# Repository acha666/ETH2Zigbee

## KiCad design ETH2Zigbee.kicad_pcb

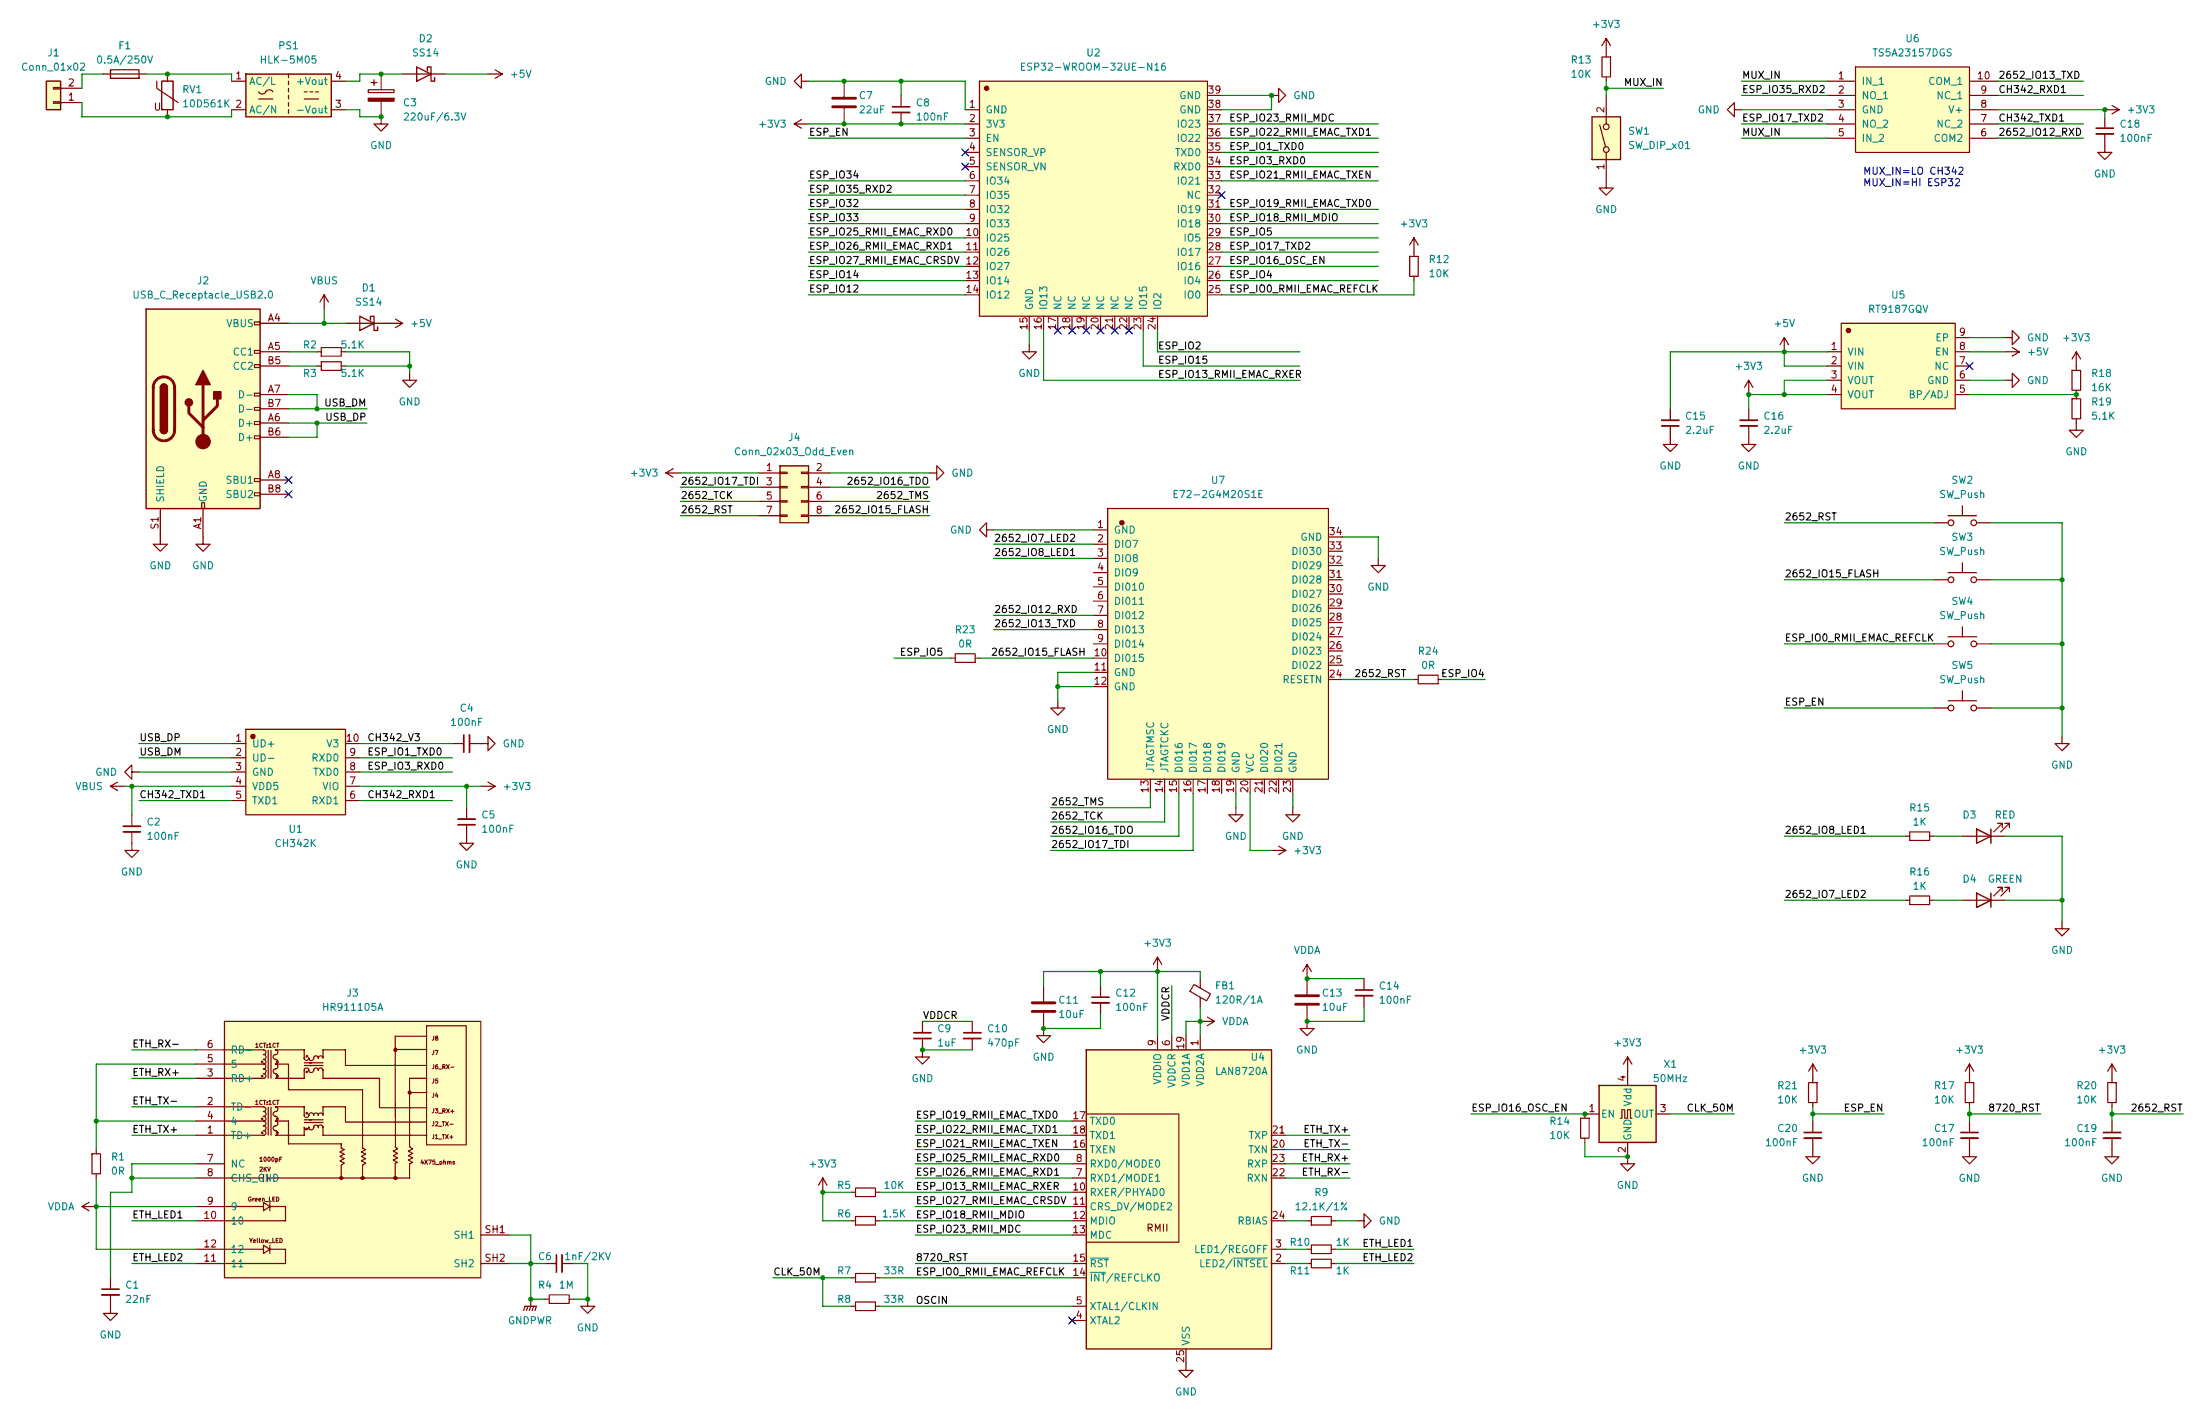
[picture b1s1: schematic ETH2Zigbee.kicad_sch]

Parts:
C1: 22nF; C_0402_1005Metric
C2, C4, C5, C8, C12, C14, C17, C18, C19, C20: 100nF; C_0402_1005Metric
C3: 220uF/6.3V; CP_Elec_6.3x5.4
C6: 1nF/2KV; C_1206_3216Metric
C7: 22uF; C_0603_1608Metric
C9: 1uF; C_0402_1005Metric
C10: 470pF; C_0402_1005Metric
C11, C13: 10uF; C_0603_1608Metric
C15, C16: 2.2uF; C_0402_1005Metric
D1, D2: SS14; D_SMA
D3: RED; LED_0402_1005Metric
D4: GREEN; LED_0402_1005Metric
F1: 0.5A/250V; Fuseholder_Littelfuse_Nano2_154x
FB1: 120R/1A; L_0402_1005Metric
J1: Conn_01x02; CONN-TH_2P-P5.00_WJ500V-5.08-2P
J2: USB_C_Receptacle_USB2.0; USB_C_Receptacle_XKB_U262-16XN-4BVC11
J3: HR911105A; RJ45-TH_HR911105A
J4: Conn_02x03_Odd_Even; PinHeader_2x04_P2.54mm_Vertical
PS1: HLK-5M05; PWRM-TH_HLK-5M05
R1, R23, R24: 0R; R_0402_1005Metric
R2, R3, R19: 5.1K; R_0402_1005Metric
R4: 1M; R_1206_3216Metric
R5, R12, R13, R14, R17, R20, R21: 10K; R_0402_1005Metric
R6: 1.5K; R_0402_1005Metric
R7, R8: 33R; R_0402_1005Metric
R9: 12.1K/1%; R_0402_1005Metric
R10, R11, R15, R16: 1K; R_0402_1005Metric
R18: 16K; R_0402_1005Metric
RV1: 10D561K; RV_Disc_D12mm_W7.1mm_P7.5mm
SW1: SW_DIP_x01; SW_DIP_SPSTx01_Slide_Copal_CHS-01A_W5.08mm_P1.27mm_JPin
SW2, SW3, SW4, SW5: SW_Push; SW_Push_SPST_NO_Alps_SKRK
U1: CH342K; SSOP-10_3.9x4.9mm_P1.00mm
U2: ESP32-WROOM-32UE-N16; WIFI-SMD_ESP32-WROOM-32E
U4: LAN8720A; VQFN-24-1EP_4x4mm_P0.5mm_EP2.5x2.5mm_ThermalVias
U5: RT9187GQV; DFN-8-1EP_3x3mm_P0.65mm_EP1.55x2.4mm
U6: TS5A23157DGS; MSOP-10_3x3mm_P0.5mm
U7: E72-2G4M20S1E; WIRELM-SMD_E72-2G4M20S1E
X1: 50MHz; Oscillator_SMD_Abracon_ASE-4Pin_3.2x2.5mm

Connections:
+3V3: C5.2, C7.2, C8.2, C11.1, C12.1, C16.2, C18.1, FB1.1, J4.1, R5.1, R6.1, R12.1, R13.1, R17.1, R18.1, R20.1, R21.1, U1.7 (VIO), U2.2 (3V3), U4.9 (VDDIO), U5.3 (VOUT), U5.4 (VOUT), U6.8 (V+), U7.20 (VCC), X1.4 (Vdd)
+5V: C15.2, D1.1 (K), D2.1 (K), U5.1 (VIN), U5.2 (VIN), U5.8 (EN)
/2652_IO7_LED2: R16.1, U7.2 (DIO7)
/2652_IO8_LED1: R15.1, U7.3 (DIO8)
/2652_IO12_RXD: U6.6 (COM2), U7.7 (DI012)
/2652_IO13_TXD: U6.10 (COM_1), U7.8 (DI013)
/2652_IO15_FLASH: J4.8, R23.1, SW3.1, U7.10 (DI015)
/2652_IO16_TDO: J4.4, U7.15 (DI016)
/2652_IO17_TDI: J4.3, U7.16 (DI017)
/2652_RST: C19.1, J4.7, R20.2, R24.2, SW2.1, U7.24 (RESETN)
/2652_TCK: J4.5, U7.14 (JTAGTCKC)
/2652_TMS: J4.6, U7.13 (JTAGTMSC)
/8720_RST: C17.1, R17.2, U4.15 (~RST)
/CH342_RXD1: U1.6 (RXD1), U6.9 (NC_1)
/CH342_TXD1: U1.5 (TXD1), U6.7 (NC_2)
/CH342_V3: C4.1, U1.10 (V3)
/CLK_50M: R7.1, R8.1, X1.3 (OUT)
/ESP_EN: C20.1, R21.2, SW5.1, U2.3 (EN)
/ESP_IO0_RMII_EMAC_REFCLK: R7.2, R12.2, SW4.1, U2.25 (IO0), U4.14 (~INT/REFCLKO)
/ESP_IO1_TXD0: U1.9 (RXD0), U2.35 (TXD0)
/ESP_IO2: U2.24 (IO2)
/ESP_IO3_RXD0: U1.8 (TXD0), U2.34 (RXD0)
/ESP_IO4: R24.1, U2.26 (IO4)
/ESP_IO5: R23.2, U2.29 (IO5)
/ESP_IO12: U2.14 (IO12)
/ESP_IO13_RMII_EMAC_RXER: R5.2, U2.16 (IO13), U4.10 (RXER/PHYAD0)
/ESP_IO14: U2.13 (IO14)
/ESP_IO15: U2.23 (IO15)
/ESP_IO16_OSC_EN: R14.1, U2.27 (IO16), X1.1 (EN)
/ESP_IO17_TXD2: U2.28 (IO17), U6.4 (NO_2)
/ESP_IO18_RMII_MDIO: R6.2, U2.30 (IO18), U4.12 (MDIO)
/ESP_IO19_RMII_EMAC_TXD0: U2.31 (IO19), U4.17 (TXD0)
/ESP_IO21_RMII_EMAC_TXEN: U2.33 (IO21), U4.16 (TXEN)
/ESP_IO22_RMII_EMAC_TXD1: U2.36 (IO22), U4.18 (TXD1)
/ESP_IO23_RMII_MDC: U2.37 (IO23), U4.13 (MDC)
/ESP_IO25_RMII_EMAC_RXD0: U2.10 (IO25), U4.8 (RXD0/MODE0)
/ESP_IO26_RMII_EMAC_RXD1: U2.11 (IO26), U4.7 (RXD1/MODE1)
/ESP_IO27_RMII_EMAC_CRSDV: U2.12 (IO27), U4.11 (CRS_DV/MODE2)
/ESP_IO32: U2.8 (IO32)
/ESP_IO33: U2.9 (IO33)
/ESP_IO34: U2.6 (IO34)
/ESP_IO35_RXD2: U2.7 (IO35), U6.2 (NO_1)
/ETH_LED1: J3.10, R10.2
/ETH_LED2: J3.11, R11.2
/ETH_RX+: J3.3 (RD+), U4.23 (RXP)
/ETH_RX-: J3.6 (RD-), U4.22 (RXN)
/ETH_TX+: J3.1 (TD+), U4.21 (TXP)
/ETH_TX-: J3.2 (TD-), U4.20 (TXN)
/MUX_IN: R13.2, SW1.2, U6.1 (IN_1), U6.5 (IN_2)
/OSCIN: R8.2, U4.5 (XTAL1/CLKIN)
/USB_DM: J2.A7 (D-), J2.B7 (D-), U1.2 (UD-)
/USB_DP: J2.A6 (D+), J2.B6 (D+), U1.1 (UD+)
/VDDCR: C9.1, C10.1, U4.6 (VDDCR)
GND: C1.2, C2.1, C3.2, C4.2, C5.1, C6.2, C7.1, C8.1, C9.2, C10.2, C11.2, C12.2, C13.2, C14.2, C15.1, C16.1, C17.2, C18.2, C19.2, C20.2, D3.1 (K), D4.1 (K), J2.A1 (GND), J2.A12 (GND), J2.B1 (GND), J2.B12 (GND), J2.S1 (SHIELD), J4.2, PS1.3 (-Vout), R2.2, R3.2, R4.2, R9.2, R14.2, R19.2, SW1.1, SW2.2, SW3.2, SW4.2, SW5.2, U1.3 (GND), U2.1 (GND), U2.15 (GND), U2.38 (GND), U2.39 (GND), U4.25 (VSS), U5.6 (GND), U5.9 (EP), U6.3 (GND), U7.1 (GND), U7.11 (GND), U7.12 (GND), U7.19 (GND), U7.23 (GND), U7.34 (GND), X1.2 (GND)
GNDPWR: C6.1, J3.SH1, J3.SH2, R4.1
unnamed: C3.1, D2.2 (A), PS1.4 (+Vout)
unnamed: D3.2 (A), R15.2
unnamed: D4.2 (A), R16.2
unnamed: J1.1, PS1.2 (AC/N), RV1.2
unnamed: F1.1, J1.2
unnamed: J2.A5 (CC1), R2.1
unnamed: J2.B5 (CC2), R3.1
unnamed: C1.1, J3.7 (NC), J3.8 (CHS_GND)
unnamed: J3.4, J3.5, R1.1
unnamed: F1.2, PS1.1 (AC/L), RV1.1
unnamed: R10.1, U4.3 (LED1/REGOFF)
unnamed: R11.1, U4.2 (LED2/~INTSEL)
unnamed: R9.1, U4.24 (RBIAS)
unnamed: R18.2, R19.1, U5.5 (BP/ADJ)
VBUS: C2.2, D1.2 (A), J2.A4 (VBUS), J2.A9 (VBUS), J2.B4 (VBUS), J2.B9 (VBUS), U1.4 (VDD5)
VDDA: C13.1, C14.1, FB1.2, J3.9, J3.12, R1.2, U4.1 (VDD2A), U4.19 (VDD1A)

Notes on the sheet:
MUX_IN=LO CH342 MUX_IN=HI ESP32

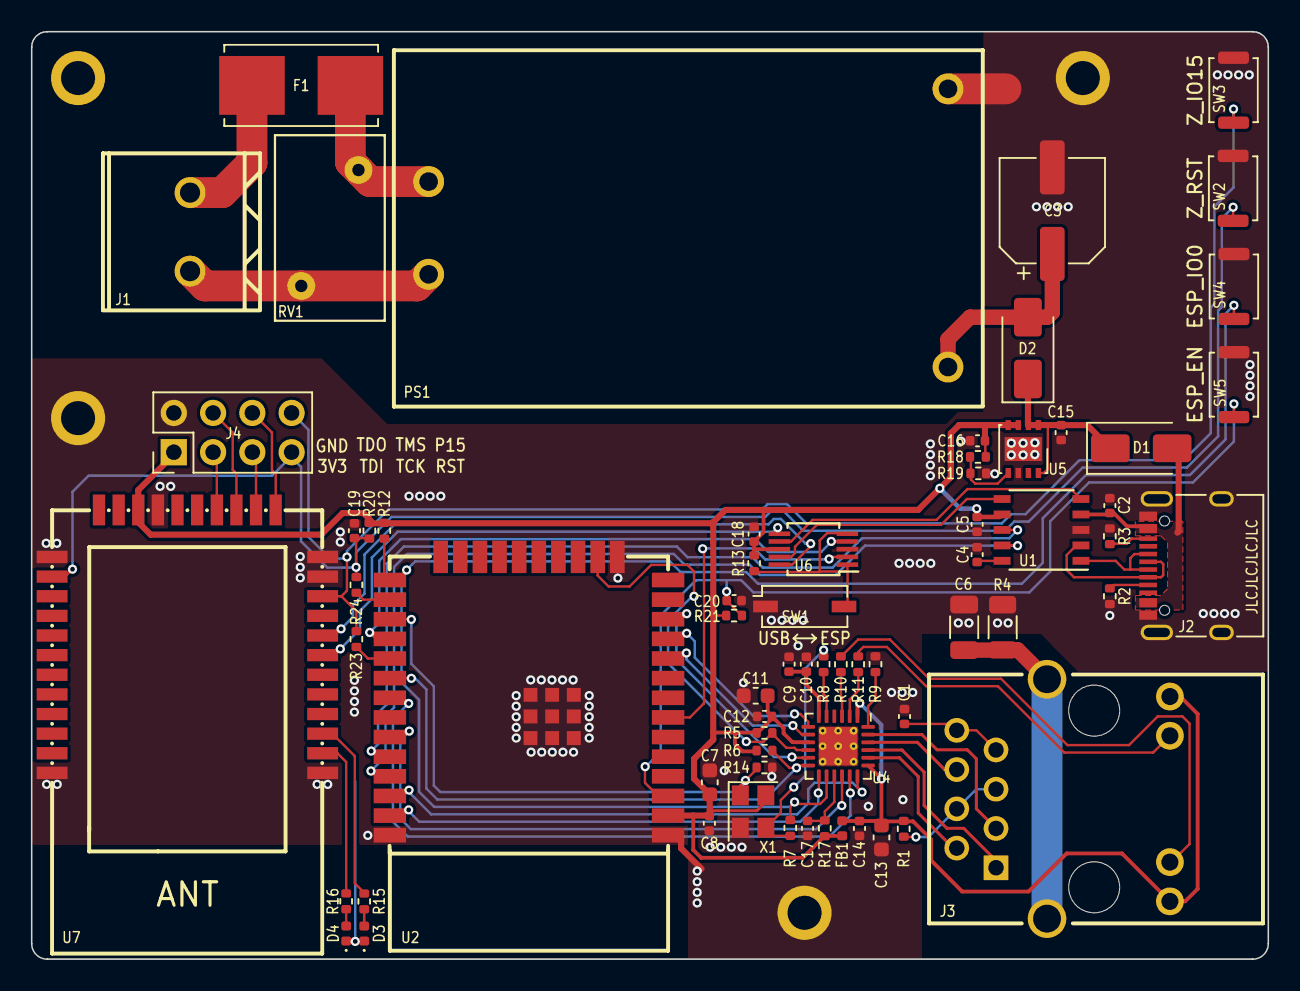
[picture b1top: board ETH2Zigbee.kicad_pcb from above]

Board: 2 copper layers, 80.0 x 60.0 mm, 67 parts (0 on the bottom side), 64 nets.
